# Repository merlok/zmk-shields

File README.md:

# ZMK-Shields

This project contains the design and firmware files for custom wireless split ergonomic keyboards I have designed.

## Repository Structure

- **kicad/**: Contains all KiCad design files, including:
  - Reversible PCB designs
  - Top and bottom plate designs for most shields

- **boards/**: Contains the ZMK firmware plugin files.

## Getting Started

### KiCad Design Files

The `kicad` directory includes all necessary files to modify and fabricate the keyboard's PCB and plates. Open these files in KiCad to view or edit the design.

### Firmware

The   firmware for the keyboard is managed using ZMK, a flexible firmware specifically designed for custom keyboards. The firmware compilation is handled using Zephyr and automated through GitHub Actions. Simply push a commit and GHA will produce the files which can be flashed as per [ZMK's flashing instructions](https://zmk.dev/docs/development/build-flash).

## Keyboard Designs

### Kestrel

The Kestrel (V1) is an ortholinear wireless split keyboard with 21 keys + rotary encoder per side.

### Nightingale

The Nightingale is an ortholinear wireless split keyboard with 20 keys + rotary encoder per side. It uses low-profile choc switches and is designed to be portable with an extensive battery life.

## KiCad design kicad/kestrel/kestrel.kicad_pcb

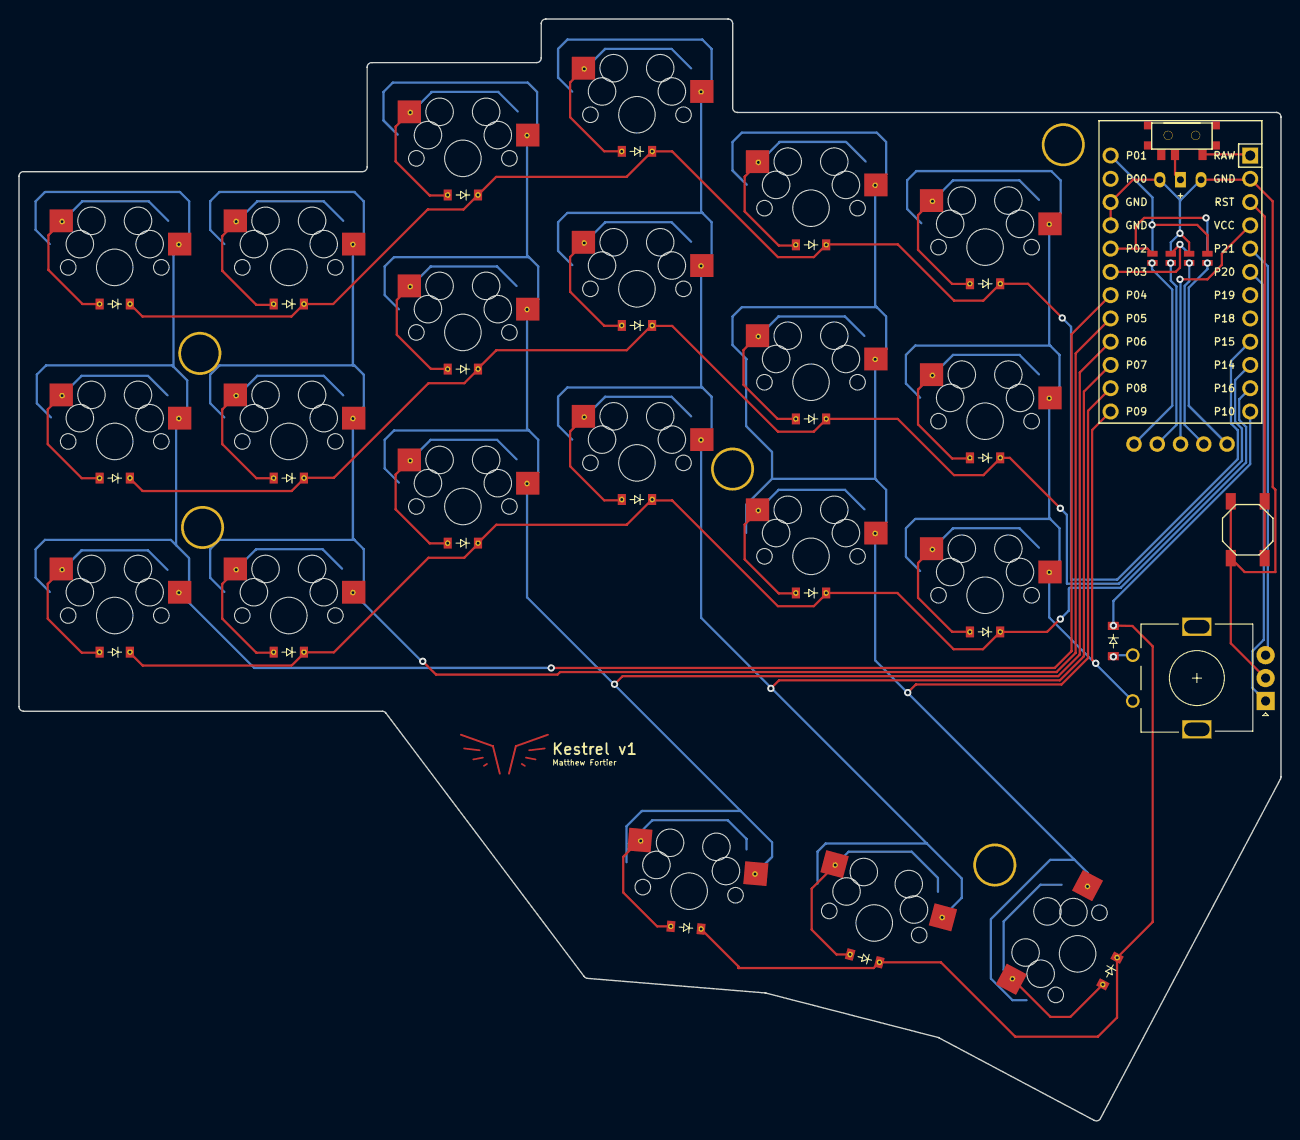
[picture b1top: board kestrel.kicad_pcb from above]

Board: 2 copper layers, 137.7 x 120.3 mm, 61 parts (0 on the bottom side), 45 nets.

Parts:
B1: SW_TACT_ALPS_SKQGABE010
D1, D2, D3, D4, D5, D6, D7, D8, D9, D10, D11, D12, D13, D14, D15, D16, D17, D18, D19, D20, D21, D22: ComboDiode
J1, J2, J3, J4, J5, J6, J7, J8: Jumper
JST REV1: JST; JST_PH_S2B-PH-K_02x2.00mm_Angled
MCU1: ProMicro
ROT1: rotary_encoder
S1, S2, S3, S4, S5, S6, S7, S8, S9, S10, S11, S12, S13, S14, S15, S16, S17, S18, S19, S20, S21: MX
T1: SPDT_C128955
TH3, TH3#2, TH3#3, TH3#4, TH3#5: HOLE; HOLE_M2_TH

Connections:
CS: J1.1, J8.1, MCU1.13
ENCA: MCU1.6, ROT1.A
ENCB: MCU1.5, ROT1.B
GND: B1.2, J3.1, J6.1, JST REV1.1, JST REV1.2, MCU1.2, MCU1.15, MCU1.16, ROT1.C
JST: JST REV1.1, T1.2
J_pad1: J7.2, J8.2
J_pad2: J5.2, J6.2
J_pad3: J3.2, J4.2
J_pad4: J1.2, J2.2
RAW: MCU1.1, T1.1
RST: B1.1, MCU1.3
SCL: J4.1, J5.1, MCU1.18
SDA: J2.1, J7.1, MCU1.17
col_0: MCU1.19, S1.1, S2.1, S3.1
col_1: MCU1.20, S4.1, S5.1, S6.1
col_2: MCU1.21, S7.1, S8.1, S9.1, S19.1
col_3: MCU1.22, S10.1, S11.1, S12.1, S20.1
col_4: MCU1.23, S13.1, S14.1, S15.1, S21.1
col_5: MCU1.24, ROT1.1, S16.1, S17.1, S18.1
far_fan: D21.2, S21.2
home_fan: D20.2, S20.2
index_bottom: D13.2, S13.2
index_home: D14.2, S14.2
index_top: D15.2, S15.2
inner_bottom: D16.2, S16.2
inner_home: D17.2, S17.2
inner_top: D18.2, S18.2
middle_bottom: D10.2, S10.2
middle_home: D11.2, S11.2
middle_top: D12.2, S12.2
near_fan: D19.2, S19.2
outer_bottom: D1.2, S1.2
outer_home: D2.2, S2.2
outer_top: D3.2, S3.2
pinkie_bottom: D4.2, S4.2
pinkie_home: D5.2, S5.2
pinkie_top: D6.2, S6.2
r_diode: D22.2, ROT1.2
ring_bottom: D7.2, S7.2
ring_home: D8.2, S8.2
ring_top: D9.2, S9.2
row_0: D19.1, D20.1, D21.1, D22.1, MCU1.12
row_1: D1.1, D4.1, D7.1, D10.1, D13.1, D16.1, MCU1.11
row_2: D2.1, D5.1, D8.1, D11.1, D14.1, D17.1, MCU1.10
row_3: D3.1, D6.1, D9.1, D12.1, D15.1, D18.1, MCU1.9

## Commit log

2024-03-07 add kestrel v1 shield
2024-03-07 modify build file
2024-03-07 fixed ENT->RET in keymap
2024-03-07 cleanup for kestrel v1
2024-07-15 dongle addition
2024-07-15 dongle config file
2024-07-15 try nice!nano firmware
2024-07-15 add spoofed col-gpios
2024-07-20 test dongle board config
2024-07-20 custom board type
2024-07-20 remove include
2024-07-20 config changes
2024-07-20 revert to nice!nano v2
2024-07-20 settings reset firmware
2024-07-20 set dongle gpios to left
2024-07-29 added nightingale for posterity
